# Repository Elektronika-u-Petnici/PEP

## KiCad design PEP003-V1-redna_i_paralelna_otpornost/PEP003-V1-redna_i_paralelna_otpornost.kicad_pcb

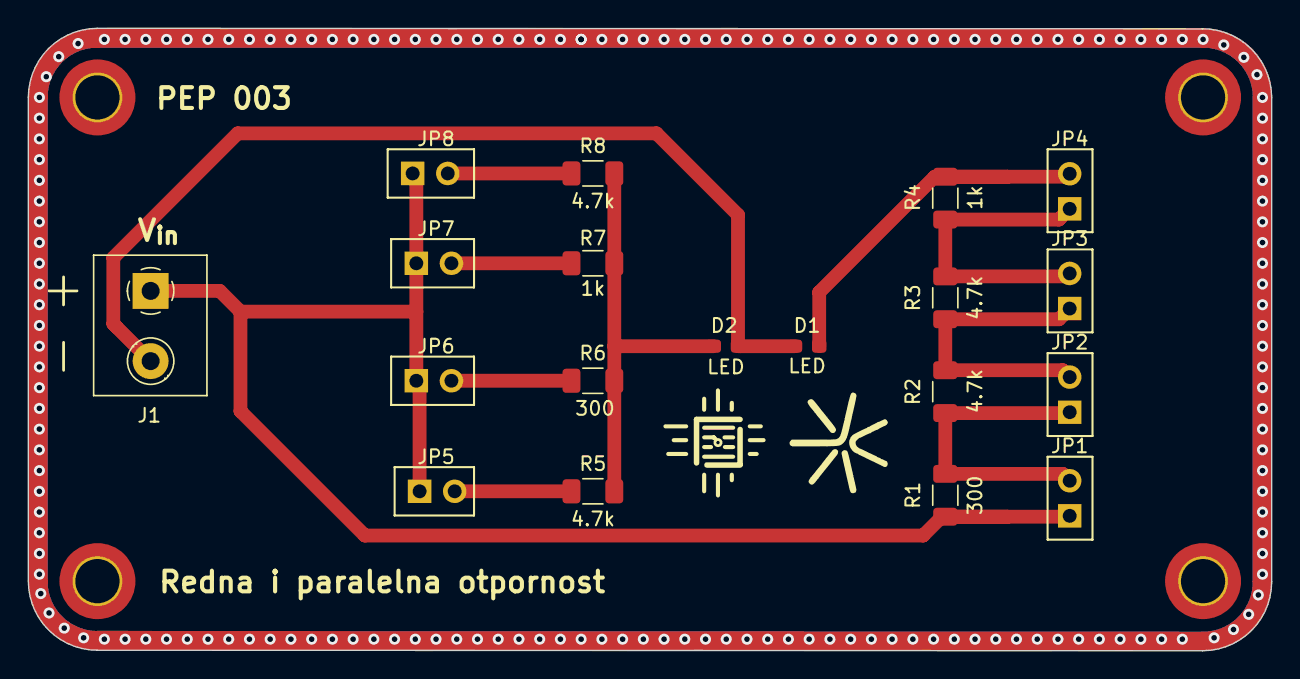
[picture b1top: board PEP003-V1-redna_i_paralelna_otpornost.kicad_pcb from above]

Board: 2 copper layers, 90.0 x 45.0 mm, 23 parts (0 on the bottom side), 2 nets.

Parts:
D1, D2: LED; LED_0603_1608Metric_Pad1.05x0.95mm_HandSolder
H1, H2, H3, H4: MountingHole; MountingHole_3.2mm_M3_ISO14580_Pad_TopBottom
J1: Screw_Terminal_01x02; TerminalBlock_Phoenix_MKDS-1,5-2-5.08_1x02_P5.08mm_Horizont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
JP1, JP2, JP3, JP4, JP5, JP6, JP7, JP8: Jumper; PinHeader_1x02_P2.54mm_Vertical
R1, R6: 300; R_smd
R2, R3, R5, R8: 4.7k; R_smd
R4, R7: 1k; R_smd

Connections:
0: D1.1 (K), D2.1 (K), J1.2
9V: J1.1, JP1.1 (A), JP5.1 (A), JP6.1 (A), JP7.1 (A), JP8.1 (A), R1.1

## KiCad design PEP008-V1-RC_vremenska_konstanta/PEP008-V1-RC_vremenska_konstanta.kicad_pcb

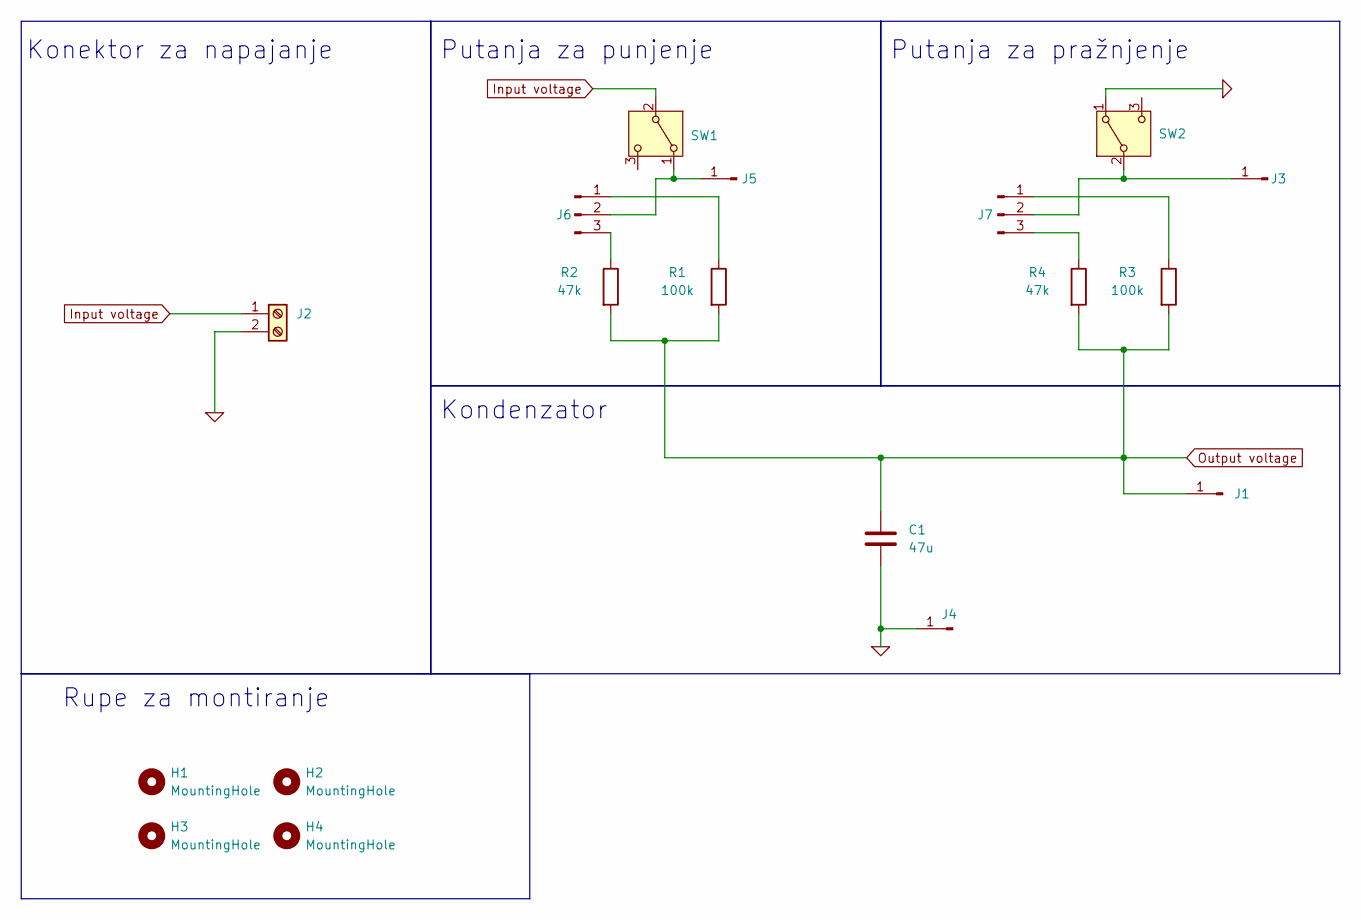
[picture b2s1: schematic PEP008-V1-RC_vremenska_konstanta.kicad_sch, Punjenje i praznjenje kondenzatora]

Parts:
C1: 47u; C_1206_3216Metric; LCSC C76659
H1, H2, H3, H4: MountingHole; MountingHole_3.2mm_M3_ISO14580_Pad_TopBottom
J1, J3, J4, J5: Conn_01x01_Pin; PinHeader_1x01_P2.54mm_Vertical
J2: Screw_Terminal_01x02; TerminalBlock_Phoenix_MKDS-1,5-2-5.08_1x02_P5.08mm_Horizont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
J6, J7: Conn_01x03_Pin; PinHeader_1x03_P2.54mm_Vertical
R1, R3: 100k; R_1206_3216Metric_Pad1.30x1.75mm_HandSolder; LCSC C17900
R2, R4: 47k; R_1206_3216Metric_Pad1.30x1.75mm_HandSolder; LCSC C25664
SW1, SW2: SW_SPDT; SW-TH_2MS1T1B1M1QES-5

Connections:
0: C1.2, J2.2, J4.1, SW2.1 (A)
Input voltage: J2.1, SW1.2 (B)
unnamed: J3.1, J7.2, SW2.2 (B)
unnamed: J5.1, J6.2, SW1.1 (A)
unnamed: J6.1, R1.1
unnamed: J6.3, R2.1
unnamed: J7.1, R3.1
unnamed: J7.3, R4.1
Output voltage: C1.1, J1.1, R1.2, R2.2, R3.2, R4.2

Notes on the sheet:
Rupe za montiranje
Kondenzator
Konektor za napajanje
Putanja za pražnjenje
Putanja za punjenje

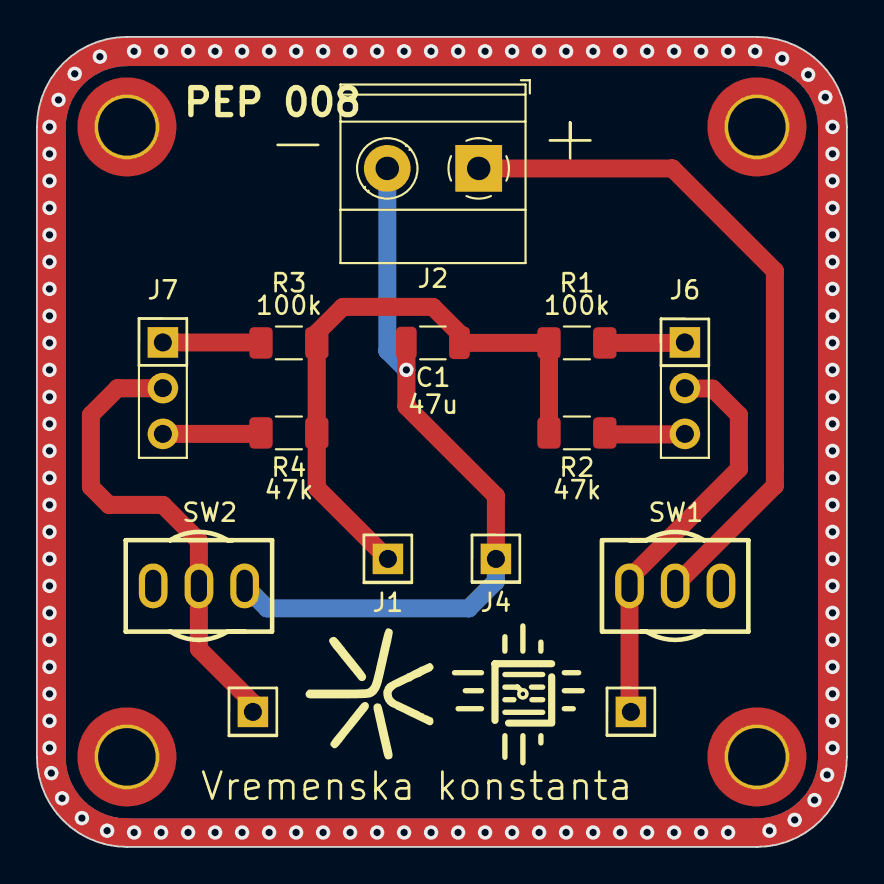
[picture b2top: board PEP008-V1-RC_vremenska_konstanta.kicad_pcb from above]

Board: 2 copper layers, 45.0 x 45.0 mm, 18 parts (0 on the bottom side), 9 nets.

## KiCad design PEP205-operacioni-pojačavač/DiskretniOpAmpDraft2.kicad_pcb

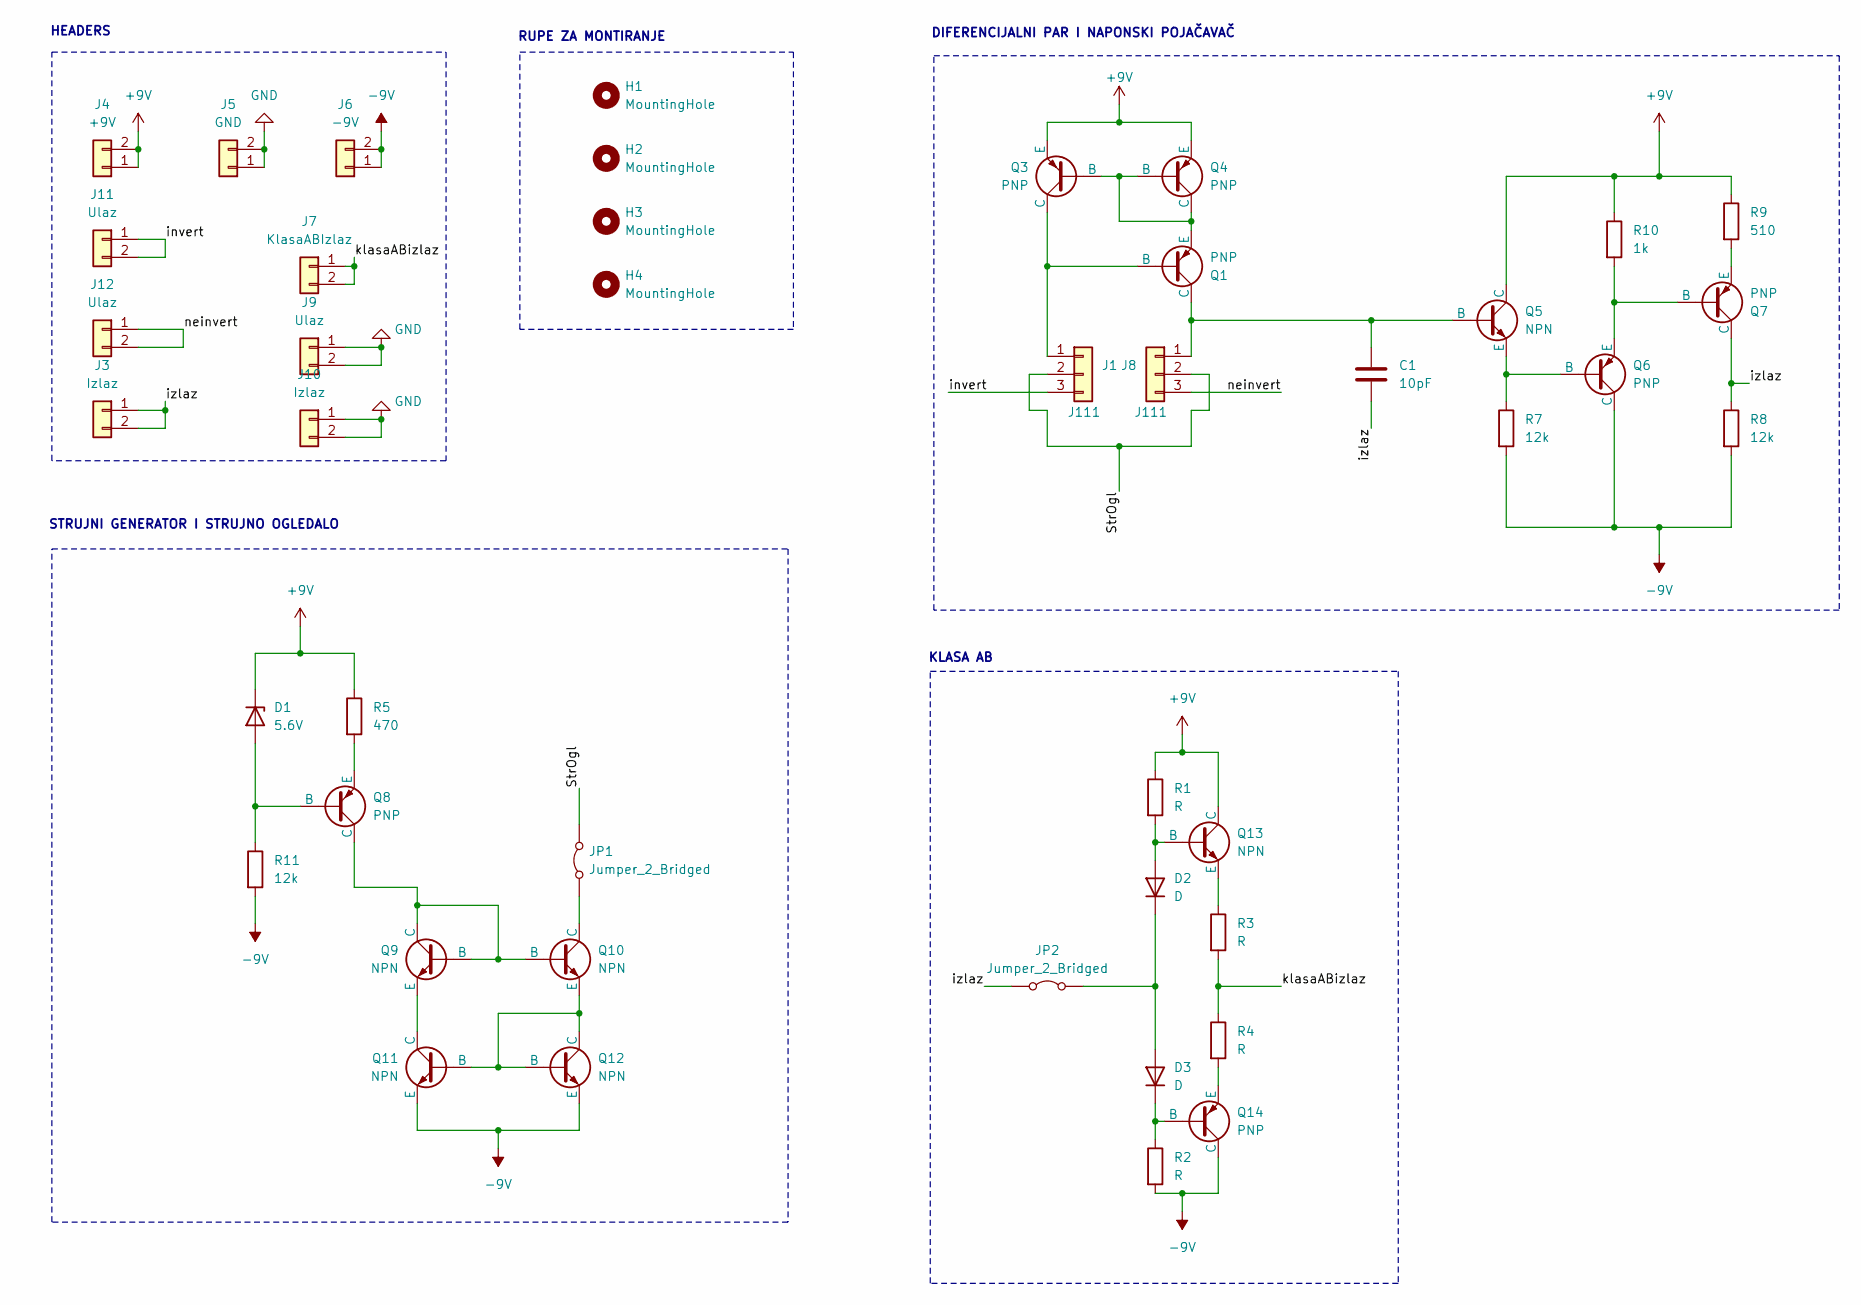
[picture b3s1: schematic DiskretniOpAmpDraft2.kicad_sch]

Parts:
C1: 10pF; C_Disc_D3.8mm_W2.6mm_P2.50mm
D1: 5.6V; D_A-405_P7.62mm_Horizontal
D2, D3: D; D_A-405_P7.62mm_Horizontal
H1, H2, H3, H4: MountingHole; MountingHole_3.2mm_M3_ISO14580_Pad_TopBottom
J1, J8: J111; PinSocket_1x03_P2.54mm_Vertical
J3, J10: Izlaz; PinSocket_1x02_P2.54mm_Vertical
J4: +9V; PinSocket_1x02_P2.54mm_Vertical
J5: GND; PinSocket_1x02_P2.54mm_Vertical
J6: -9V; PinSocket_1x02_P2.54mm_Vertical
J7: KlasaABIzlaz; PinSocket_1x02_P2.54mm_Vertical
J9, J11, J12: Ulaz; PinSocket_1x02_P2.54mm_Vertical
JP1, JP2: Jumper_2_Bridged; PinHeader_1x02_P2.54mm_Vertical
Q1, Q4, Q6, Q7, Q8, Q14: PNP; TO-92
Q3: PNP; TO-92L_Inline
Q5, Q9, Q10: NPN; TO-92L_Inline
Q11, Q12, Q13: NPN; TO-92
R1, R2, R3, R4: R; R_Axial_DIN0207_L6.3mm_D2.5mm_P10.16mm_Horizontal
R5: 470; R_Axial_DIN0207_L6.3mm_D2.5mm_P10.16mm_Horizontal
R7, R8, R11: 12k; R_Axial_DIN0207_L6.3mm_D2.5mm_P10.16mm_Horizontal
R9: 510; R_Axial_DIN0207_L6.3mm_D2.5mm_P10.16mm_Horizontal
R10: 1k; R_Axial_DIN0207_L6.3mm_D2.5mm_P10.16mm_Horizontal

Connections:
+9V: D1.1 (K), J4.1, J4.2, Q3.3 (E), Q4.3 (E), Q5.1 (C), Q13.1 (C), R1.1, R5.1, R9.1, R10.1
-9V: J6.1, J6.2, Q6.1 (C), Q11.3 (E), Q12.3 (E), Q14.1 (C), R2.2, R7.2, R8.2, R11.2
/StrOgl: J1.2, J8.2, JP1.2 (B)
/invert: J1.3, J11.1, J11.2
/izlaz: C1.2, J3.1, J3.2, JP2.1 (A), Q7.1 (C), R8.1
/klasaABizlaz: J7.1, J7.2, R3.2, R4.1
/neinvert: J8.3, J12.1, J12.2
GND: J5.1, J5.2, J9.1, J9.2, J10.1, J10.2
unnamed: D1.2 (A), Q8.2 (B), R11.1
unnamed: D2.2 (A), Q13.2 (B), R1.2
unnamed: D2.1 (K), D3.2 (A), JP2.2 (B)
unnamed: D3.1 (K), Q14.2 (B), R2.1
unnamed: J1.1, Q1.2 (B), Q3.1 (C)
unnamed: C1.1, J8.1, Q1.1 (C), Q5.2 (B)
unnamed: JP1.1 (A), Q10.1 (C)
unnamed: Q1.3 (E), Q3.2 (B), Q4.1 (C), Q4.2 (B)
unnamed: Q5.3 (E), Q6.2 (B), R7.1
unnamed: Q6.3 (E), Q7.2 (B), R10.2
unnamed: Q7.3 (E), R9.2
unnamed: Q8.3 (E), R5.2
unnamed: Q8.1 (C), Q9.1 (C), Q9.2 (B), Q10.2 (B)
unnamed: Q10.3 (E), Q11.2 (B), Q12.1 (C), Q12.2 (B)
unnamed: Q9.3 (E), Q11.1 (C)
unnamed: Q13.3 (E), R3.1
unnamed: Q14.3 (E), R4.2

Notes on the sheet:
KLASA AB
STRUJNI GENERATOR I STRUJNO OGLEDALO
HEADERS
DIFERENCIJALNI PAR I NAPONSKI POJAČAVAČ
RUPE ZA MONTIRANJE

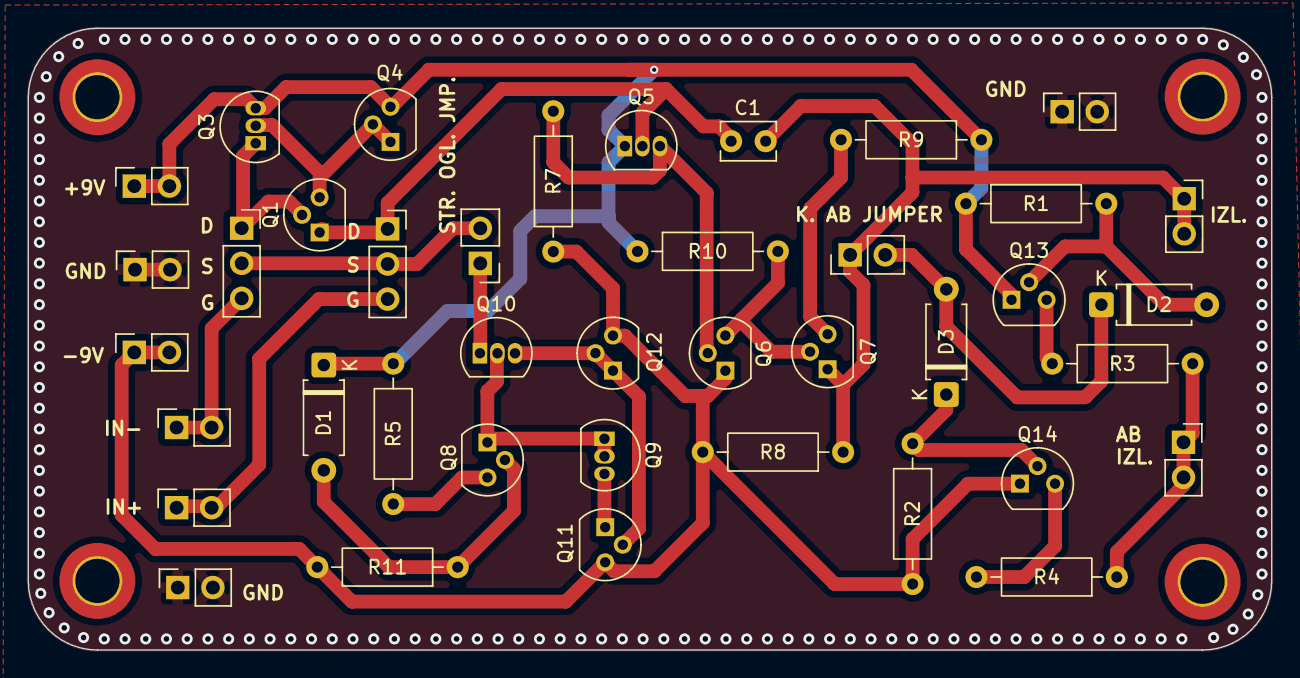
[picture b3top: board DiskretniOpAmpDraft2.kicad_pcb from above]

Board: 2 copper layers, 90.0 x 45.0 mm, 44 parts (0 on the bottom side), 25 nets.

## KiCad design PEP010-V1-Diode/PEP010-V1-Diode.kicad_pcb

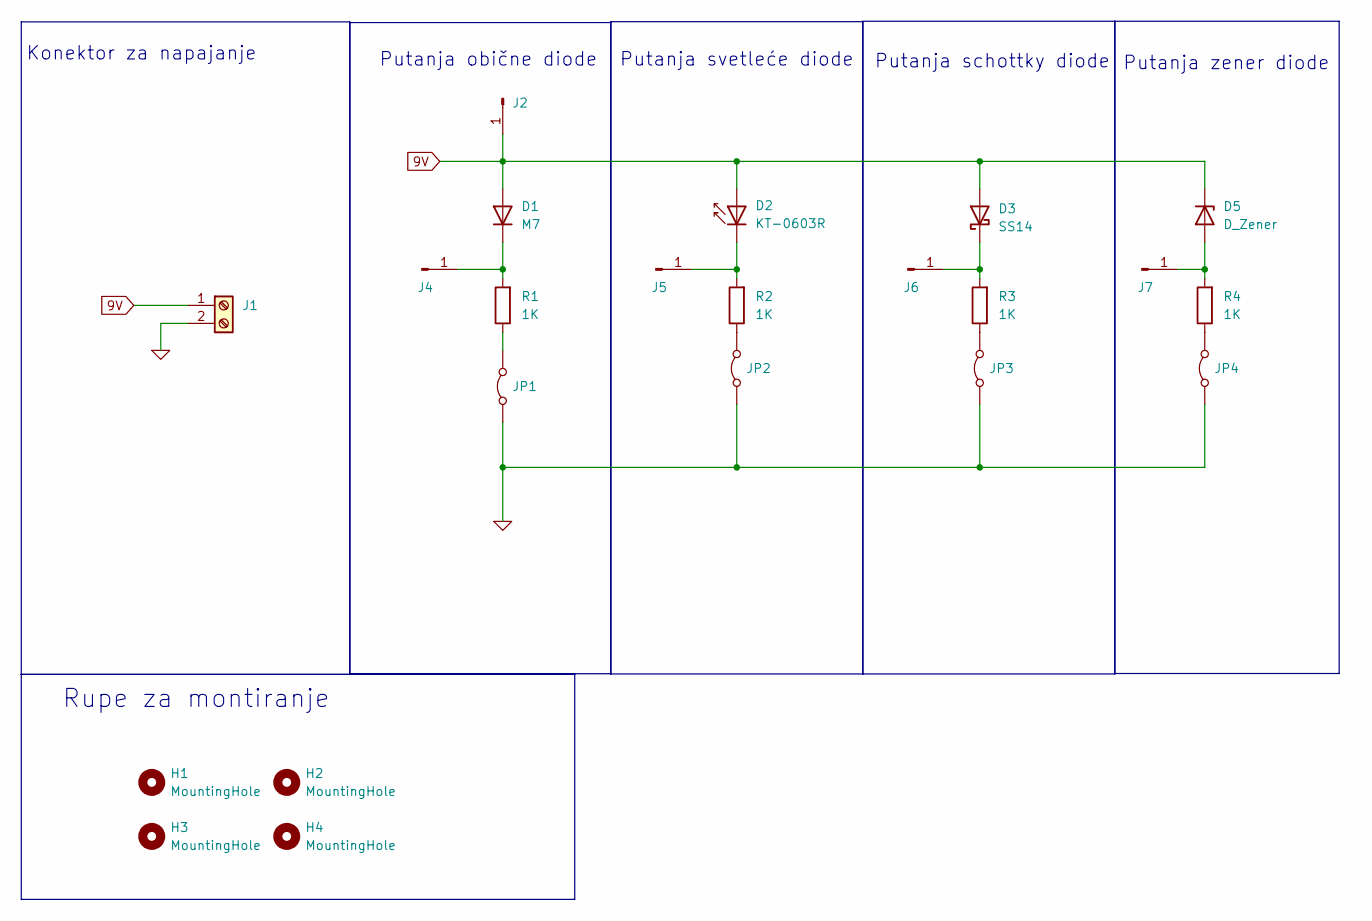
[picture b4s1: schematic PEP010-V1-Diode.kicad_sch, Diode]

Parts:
D1: M7; D_SMA; LCSC C95872
D2: KT-0603R; D_0603; LCSC C2286
D3: SS14; D_SMA; LCSC C2480
D5: D_Zener; D_A-405_P7.62mm_Horizontal
H1, H2, H3, H4: MountingHole; MountingHole_3.2mm_M3_ISO14580_Pad_TopBottom
J1: Screw_Terminal_01x02; TerminalBlock_Phoenix_MKDS-1,5-2-5.08_1x02_P5.08mm_Horizont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
J2, J4, J5, J6, J7: Conn_01x01_Pin; PinHeader_1x01_P2.54mm_Vertical
JP1, JP2, JP3, JP4: Jumper_2_Bridged; PinHeader_1x02_P2.54mm_Vertical
R1, R2, R3, R4: 1K; R_1206_3216Metric; LCSC C4410

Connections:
0: J1.2, JP1.1 (A), JP2.1 (A), JP3.1 (A), JP4.1 (A)
9V: D1.2 (A), D2.2 (A), D3.2 (A), D5.1 (K), J1.1, J2.1
unnamed: D1.1 (K), J4.1, R1.2
unnamed: D2.1 (K), J5.1, R2.2
unnamed: D3.1 (K), J6.1, R3.2
unnamed: D5.2 (A), J7.1, R4.2
unnamed: JP1.2 (B), R1.1
unnamed: JP2.2 (B), R2.1
unnamed: JP3.2 (B), R3.1
unnamed: JP4.2 (B), R4.1

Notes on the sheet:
Rupe za montiranje
Putanja svetleće diode
Konektor za napajanje
Putanja obične diode
Putanja schottky diode
Putanja zener diode

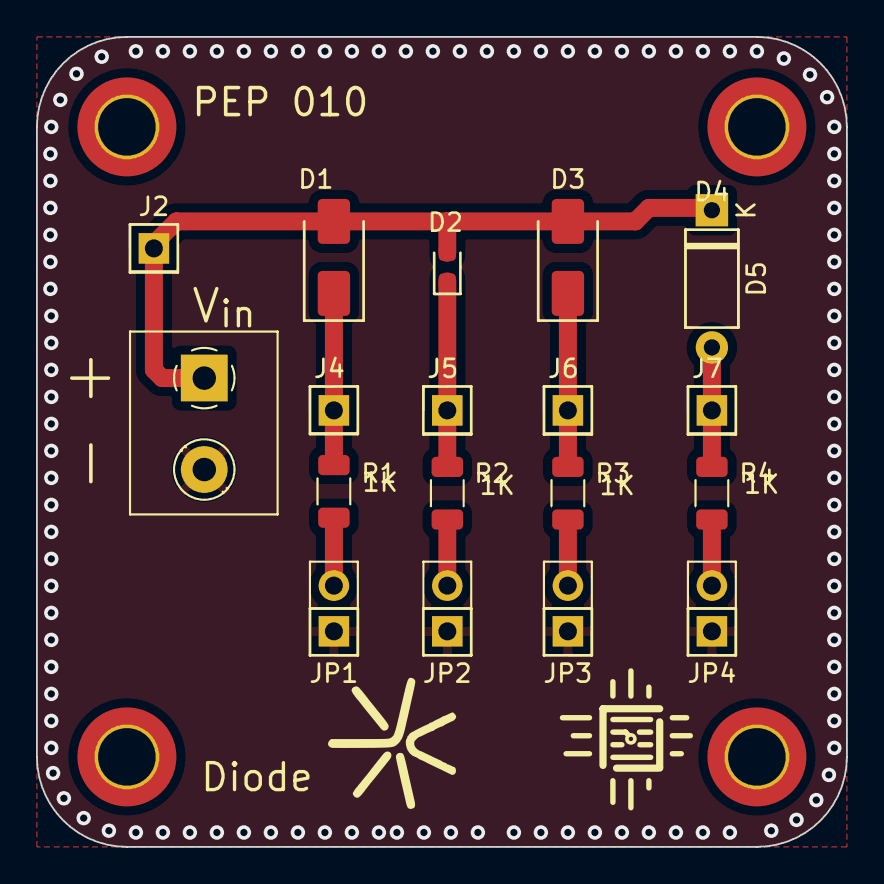
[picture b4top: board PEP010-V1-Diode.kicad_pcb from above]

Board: 2 copper layers, 45.0 x 45.0 mm, 22 parts (0 on the bottom side), 10 nets.

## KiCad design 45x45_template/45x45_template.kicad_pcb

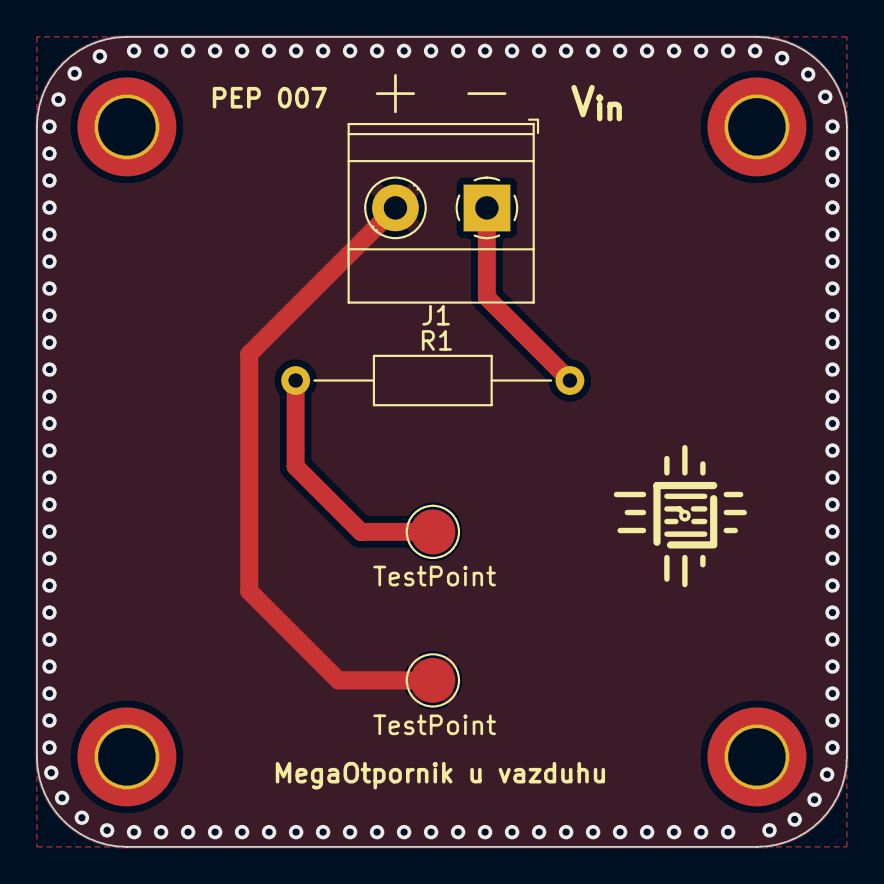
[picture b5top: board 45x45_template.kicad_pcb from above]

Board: 2 copper layers, 45.0 x 45.0 mm, 8 parts (0 on the bottom side), 3 nets.

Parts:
H1, H2, H3, H4: MountingHole; MountingHole_3.2mm_M3_ISO14580_Pad_TopBottom
J1: Screw_Terminal_01x02; TerminalBlock_Phoenix_MKDS-1,5-2-5.08_1x02_P5.08mm_Horizont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
R1: 1Meg; R_Axial_DIN0207_L6.3mm_D2.5mm_P15.24mm_Horizontal
TP2, TP2#2: TestPoint; TestPoint_Pad_D2.5mm

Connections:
0: J1.2, TP2#2.2 (1)
Input voltage: J1.1, R1.2
unnamed: R1.1, TP2.1

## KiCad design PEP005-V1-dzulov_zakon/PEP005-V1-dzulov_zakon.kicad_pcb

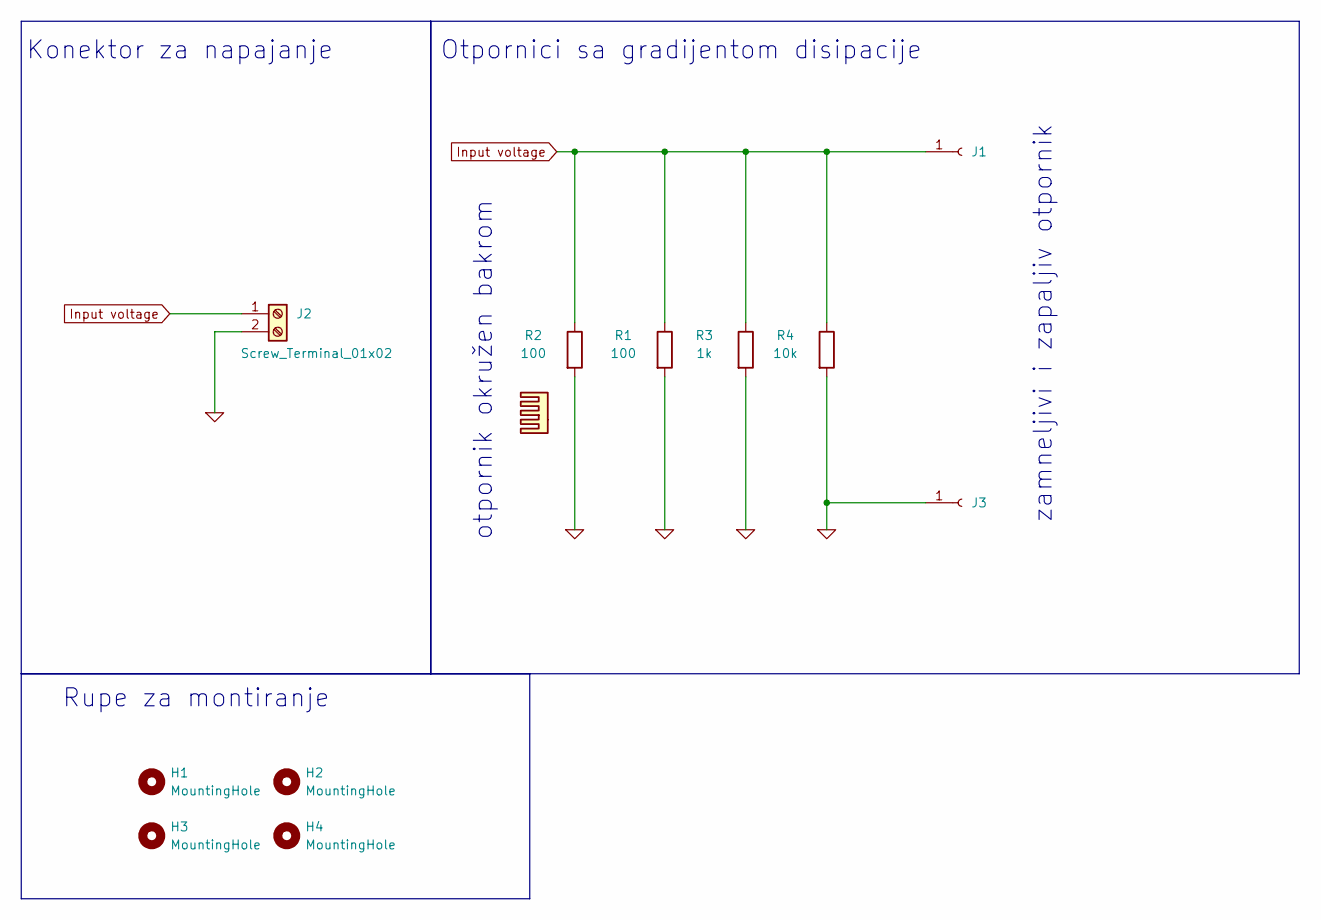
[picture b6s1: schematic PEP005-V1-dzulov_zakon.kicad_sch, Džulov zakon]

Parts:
H1, H2, H3, H4: MountingHole; MountingHole_3.2mm_M3_ISO14580_Pad_TopBottom
HS1: Heatsink
J1, J3: Conn_01x01_Socket; PinSocket_1x01_P2.54mm_Vertical
J2: Screw_Terminal_01x02; TerminalBlock_Phoenix_MKDS-1,5-2-5.08_1x02_P5.08mm_Horizont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; LCSC Part Number C3018698
R1, R2: 100; R_smd_1206; LCSC Part Number C17900
R3: 1k; R_smd_1206; LCSC Part Number C17900
R4: 10k; R_smd_1206; LCSC Part Number C17900

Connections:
0: J2.2, J3.1, R1.2, R2.2, R3.2, R4.2
Input voltage: J1.1, J2.1, R1.1, R2.1, R3.1, R4.1

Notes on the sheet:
zamneljivi i zapaljiv otpornik
Rupe za montiranje
otpornik okružen bakrom
Konektor za napajanje
Otpornici sa gradijentom disipacije

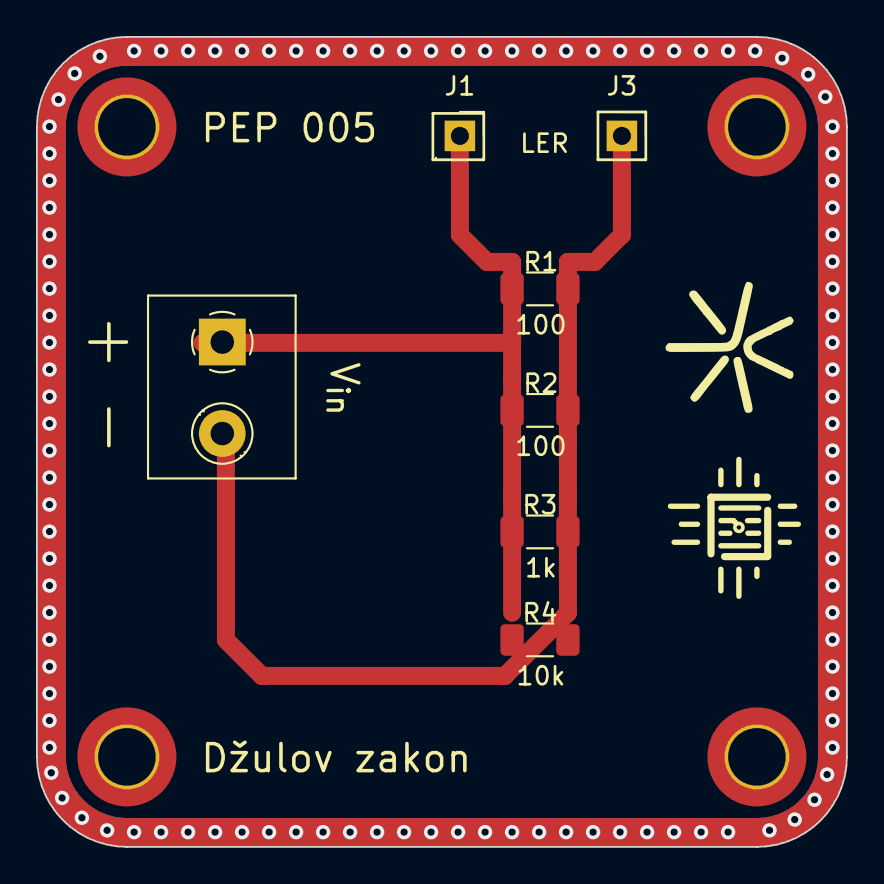
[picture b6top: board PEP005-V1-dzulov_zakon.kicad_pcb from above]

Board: 2 copper layers, 45.0 x 45.0 mm, 11 parts (0 on the bottom side), 2 nets.

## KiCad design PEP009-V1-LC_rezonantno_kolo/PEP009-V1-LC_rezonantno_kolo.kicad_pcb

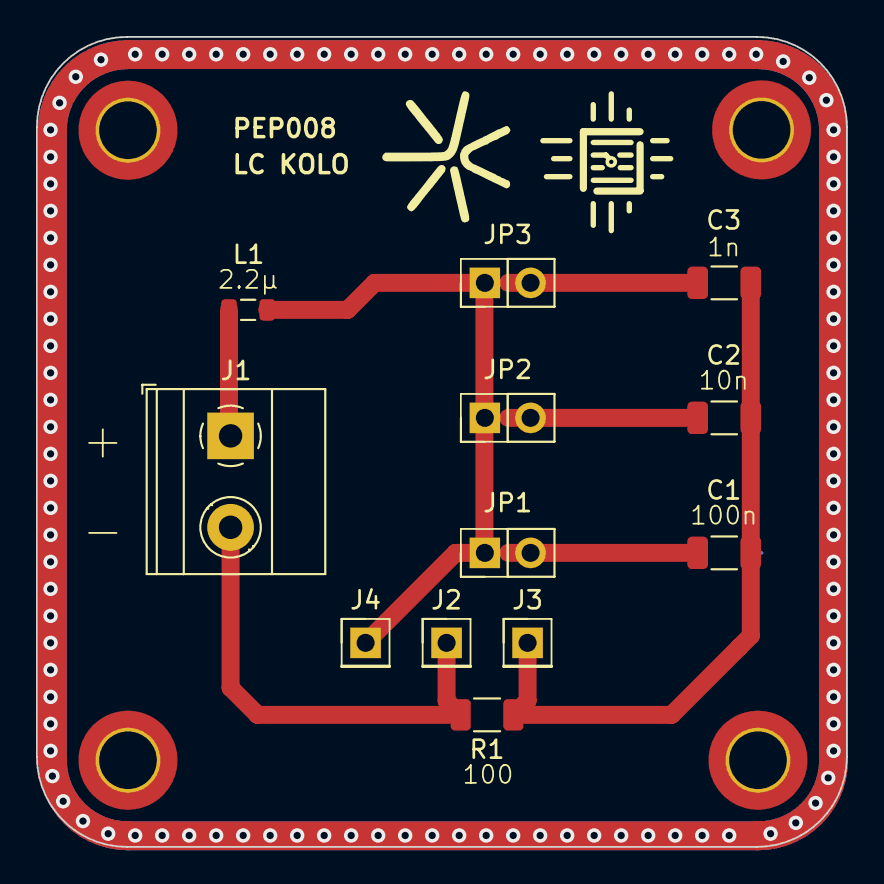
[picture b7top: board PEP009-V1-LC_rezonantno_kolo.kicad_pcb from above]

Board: 2 copper layers, 45.0 x 45.0 mm, 16 parts (0 on the bottom side), 7 nets.

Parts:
C1: 100n; C_1206_3216Metric
C2: 10n; C_1206_3216Metric
C3: 1n; C_1206_3216Metric
H1, H2, H3, H4: MountingHole; MountingHole_3.2mm_M3_ISO14580_Pad_TopBottom
J1: Screw_Terminal_01x02; TerminalBlock_Phoenix_MKDS-1,5-2-5.08_1x02_P5.08mm_Horizont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
J2, J3, J4: Conn_01x01_Pin; PinHeader_1x01_P2.54mm_Vertical
JP1, JP2, JP3: Jumper; PinHeader_1x02_P2.54mm_Vertical
L1: 2.2µ; L_0805_2012Metric
R1: 100; R_1206_3216Metric

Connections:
GND: J1.2, J2.1, R1.2
Input voltage: J1.1, L1.1
unnamed: C1.2, C2.2, C3.2, J3.1, R1.1
unnamed: J4.1, JP1.1 (A), JP2.1 (A), JP3.1 (A), L1.2
unnamed: C1.1, JP1.2 (B)
unnamed: C2.1, JP2.2 (B)
unnamed: C3.1, JP3.2 (B)

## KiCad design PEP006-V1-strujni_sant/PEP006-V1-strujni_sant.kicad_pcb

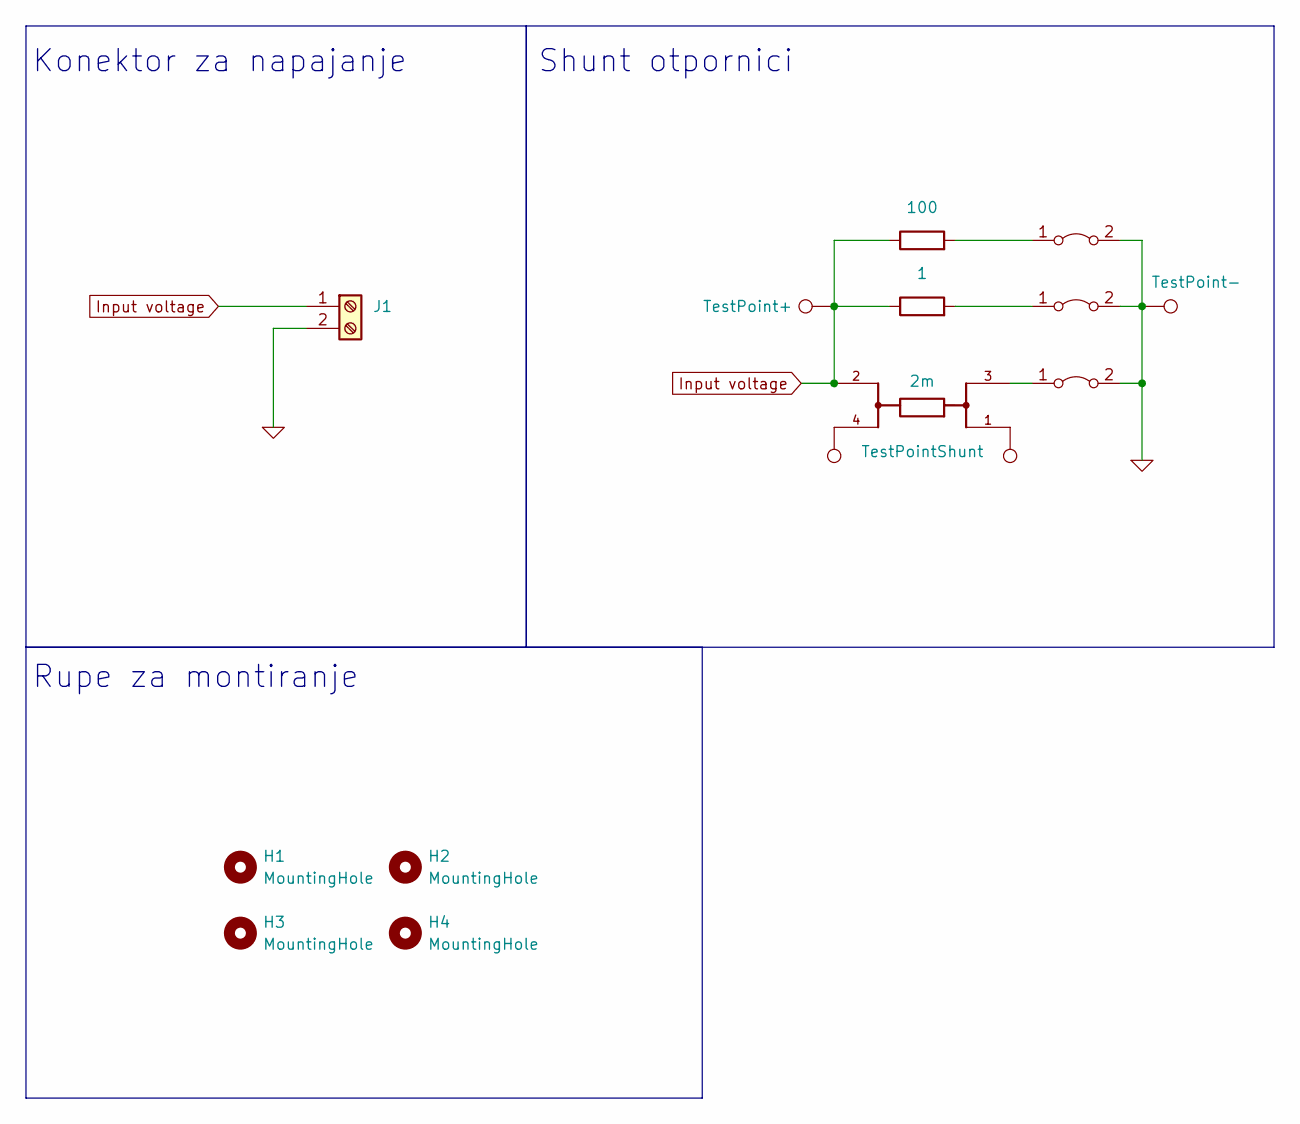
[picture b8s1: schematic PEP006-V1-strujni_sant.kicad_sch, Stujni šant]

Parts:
H1, H2, H3, H4: MountingHole; MountingHole_3.2mm_M3_ISO14580_Pad_TopBottom
J1: Screw_Terminal_01x02; TerminalBlock_Phoenix_MKDS-1,5-2-5.08_1x02_P5.08mm_Horizont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
JP1, JP2: Jumper; PinHeader_1x02_P2.54mm_Vertical
JP3: Jumper; PinHeader_1x02_P2.54mm_Vertical; LCSC C124375
R1: 2m; RES_WSK12161L000FEA; PARTREV 02-Aug-2024
R3: 100; R_1206_3216Metric_Pad1.30x1.75mm_HandSolder; LCSC C17900
R4: 1; R_1206_3216Metric_Pad1.30x1.75mm_HandSolder; LCSC C17902
TP3: TestPoint+; PinHeader_1x01_P2.54mm_Vertical
TP6, TP7: TestPointShunt; PinHeader_1x01_P2.54mm_Vertical
TP8: TestPoint-; PinHeader_1x01_P2.54mm_Vertical

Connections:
0: J1.2, JP1.2 (B), JP2.2 (B), JP3.2 (B), TP8.1
Input voltage: J1.1, R1.2, R3.1, R4.1, TP3.1
unnamed: JP1.1 (A), R3.2
unnamed: JP2.1 (A), R4.2
unnamed: JP3.1 (A), R1.3
unnamed: R1.1, TP7.1
unnamed: R1.4, TP6.1

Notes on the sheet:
Konektor za napajanje
Shunt otpornici
Rupe za montiranje

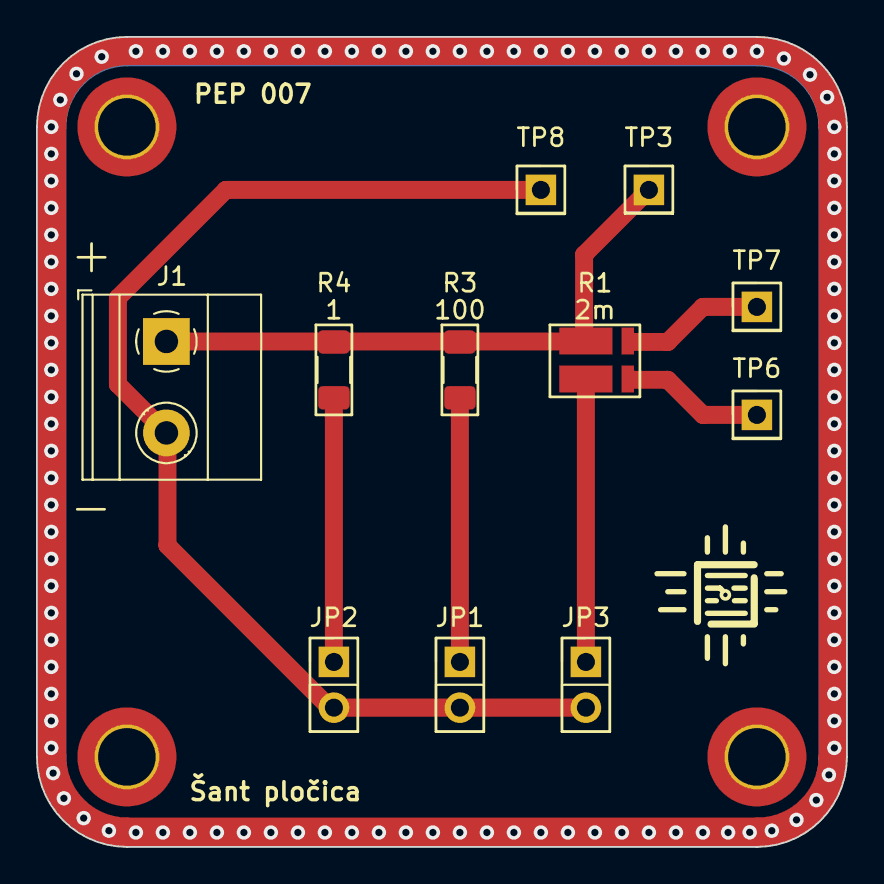
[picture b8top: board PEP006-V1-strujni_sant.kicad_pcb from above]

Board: 2 copper layers, 45.0 x 45.0 mm, 15 parts (0 on the bottom side), 7 nets.

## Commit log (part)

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2025-03-06 PEP001-V1_BOM_CPL
    -Added JLC component numbers
    -Generated BOM csv file for SMD components
    -Generated CPL csv file for SMD components
2025-03-06 Component info
    Generated csv file with all component datasheets and LCSC part numbers for future reference
2025-03-06 BOM and CPL files
    -Added LCSC information
    -Generated component info csv file for future reference
    -Generated BOM csv file
    -Generated CPL csv file
2026-02-24 Dodat PEP102, gotova šema sa oba fet-a
2026-02-24 Uklonjen PMOS sa PEP102 jer nema prostora.
2026-02-26 Placement done.
2026-02-26 Done, kinda
2026-02-26 fixed mosfet error
2026-03-01 PEP204
2026-03-02 PEP204 promena silka
2026-03-03 bjt and mosfet need to be redesigned.
2026-03-04 MOSFET updated.
2026-03-04 fork
2026-03-04 PEP201 i PEP204 :)
2026-03-05 PEP201 prepared.
2026-03-05 PEP204 prepared.
2026-03-09 Sredjena estetika simulacije, dodati komentari.
2026-03-09 Edge vias 0.
2026-03-09 Added class AB.
2026-03-10 Nova estetika.
2026-03-10 ESTETIKKAA.
2026-03-11 auto PCB render script.
2026-03-11 PEP004.
2026-03-14 Edge vias 0.
    Merge attempt.
2026-03-14 Nova estetika.
    Merge attempt 2
2026-03-14 PEP004.
    2
